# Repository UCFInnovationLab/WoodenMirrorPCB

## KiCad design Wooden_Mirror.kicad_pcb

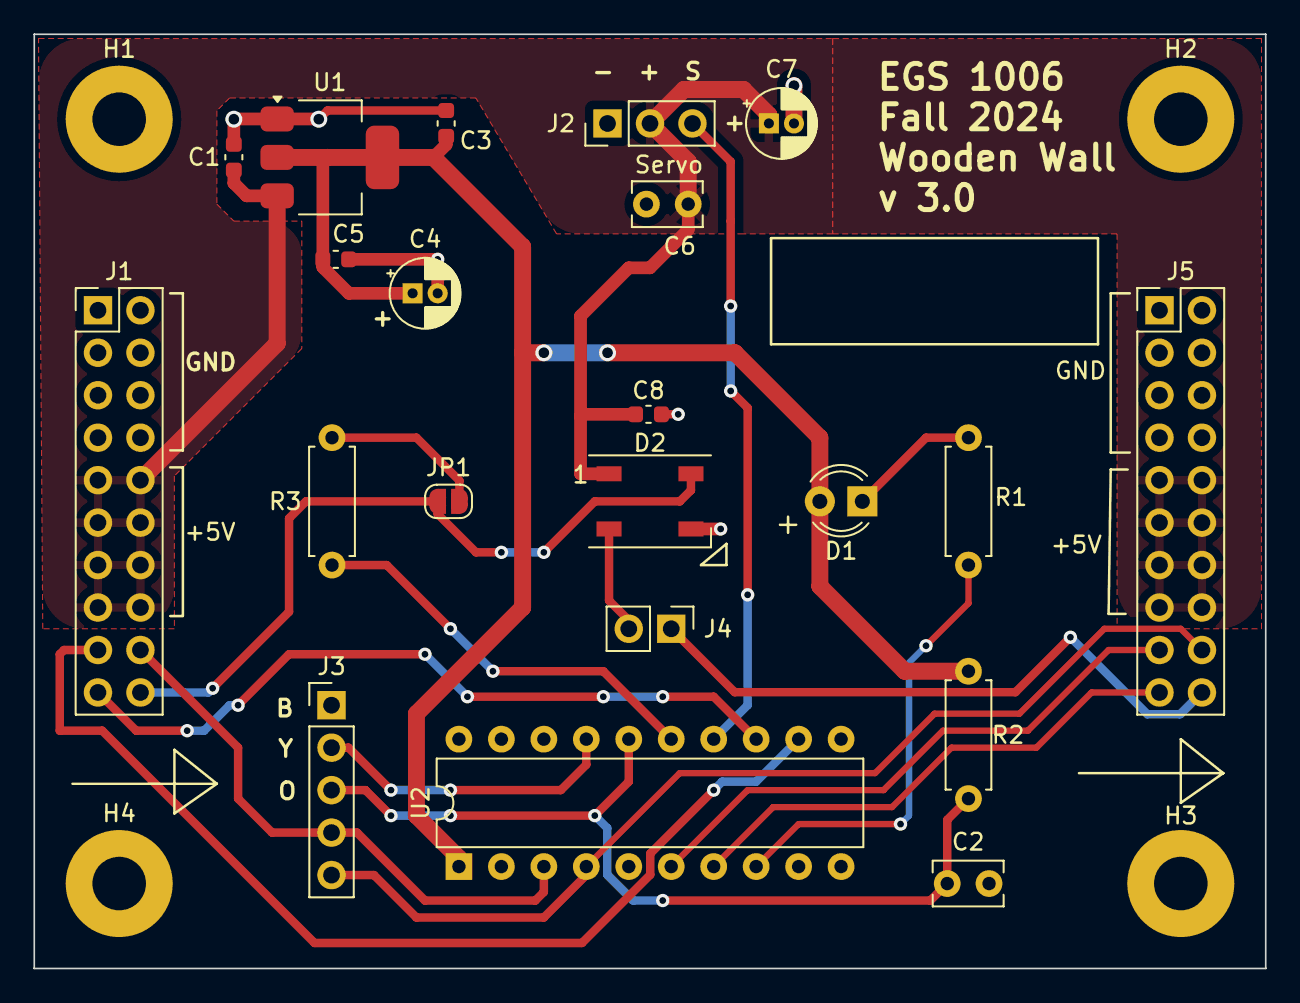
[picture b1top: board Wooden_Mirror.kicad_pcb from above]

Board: 2 copper layers, 73.7 x 55.9 mm, 25 parts (0 on the bottom side), 19 nets.

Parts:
C1, C5, C8: 100nf; C_0603_1608Metric
C2: 1nf; C_Rect_L4.0mm_W2.5mm_P2.50mm
C3: 1uf; C_0603_1608Metric
C4, C7: 10uf; CP_Radial_D4.0mm_P1.50mm
C6: 100nf; C_Rect_L4.0mm_W2.5mm_P2.50mm
D1: LED; LED_D3.0mm
D2: WS2812B; LED_WS2812B_PLCC4_5.0x5.0mm_P3.2mm
H1, H2, H3, H4: MH; MountingHole_3.2mm_M3_Pad
J1, J5: Conn_02x10_Odd_Even; PinHeader_2x10_P2.54mm_Vertical
J2: Servo; PinHeader_1x03_P2.54mm_Vertical
J3: Programmer; PinHeader_1x05_P2.54mm_Vertical
J4: LED_CHAIN; PinHeader_1x02_P2.54mm_Vertical
JP1: Local_LED_Control; SolderJumper-2_P1.3mm_Open_RoundedPad1.0x1.5mm
R1, R3: 470; R_Axial_DIN0207_L6.3mm_D2.5mm_P7.62mm_Horizontal
R2: 47k; R_Axial_DIN0207_L6.3mm_D2.5mm_P7.62mm_Horizontal
U1: TLV1117-33; SOT-223-3_TabPin2
U2: MSP430G2233IN20; DIP-20_W7.62mm

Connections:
+3V3: C3.1, C4.1, C5.1, D1.2 (A), R2.1, U1.2 (VO), U2.1 (DVCC)
+5V: C1.1, C6.1, C7.1, C8.1, D2.1 (VDD), J1.9, J1.10, J1.11, J1.12, J1.13, J1.14, J1.15, J1.16, J2.2, J5.9, J5.10, J5.11, J5.12, J5.13, J5.14, J5.15, J5.16, U1.3 (VI)
/LED_DIN: D2.4 (DIN), J1.20, JP1.1 (A)
/LED_DOUT: J4.1, J5.20
/SBWTCK: J3.2, U2.17 (TEST/SBWTCK)
/SBWTDIO: C2.1, J3.3, R2.2, U2.16 (~RST/NMI/SBWTDIO)
/Serial_IN: J1.18, J3.4, U2.3 (TA0.0/UCA0RXD/UCA0SOMI/A1/P1.1)
/Serial_OUT: J3.5, J5.18, U2.4 (TA0.1/UCA0TXD/UCA0SIMO/A2/P1.2)
GND: C1.2, C2.2, C3.2, C4.2, C5.2, C6.2, C7.2, C8.2, D2.3 (VSS), H1.1, H2.1, H3.1, H4.1, J1.1, J1.2, J1.3, J1.4, J1.5, J1.6, J1.7, J1.8, J2.1, J3.1, J5.1, J5.2, J5.3, J5.4, J5.5, J5.6, J5.7, J5.8, U1.1 (GND), U2.20 (DVSS)
unnamed: D1.1 (K), R1.1
unnamed: D2.2 (DOUT), J4.2
unnamed: J1.17, U2.12 (P2.4/TA1.2)
unnamed: J1.19, U2.13 (P2.5/TA1.2)
unnamed: J2.3, U2.14 (TDI/TCLK/TA0.1/UCB0SOMI/UCB0SCL/A6/P1.6)
unnamed: J5.17, U2.6 (TCK/SMCLK/UCB0STE/UCA0CLK/VREF+/VeREF+/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)
unnamed: J5.19, U2.7 (TMS/TA0.0/UCB0CLK/UCA0STE/A5/P1.5)
unnamed: JP1.2 (B), R3.2
unnamed: R1.2, U2.8 (P2.0/TA1.0)
unnamed: R3.1, U2.15 (TDO/TDI/UCB0SIMO/UCB0SDA/A7/P1.7)

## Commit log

2024-08-27 Sent V2
2024-09-06 V3 sent to JCLPCB
2024-09-23 later
